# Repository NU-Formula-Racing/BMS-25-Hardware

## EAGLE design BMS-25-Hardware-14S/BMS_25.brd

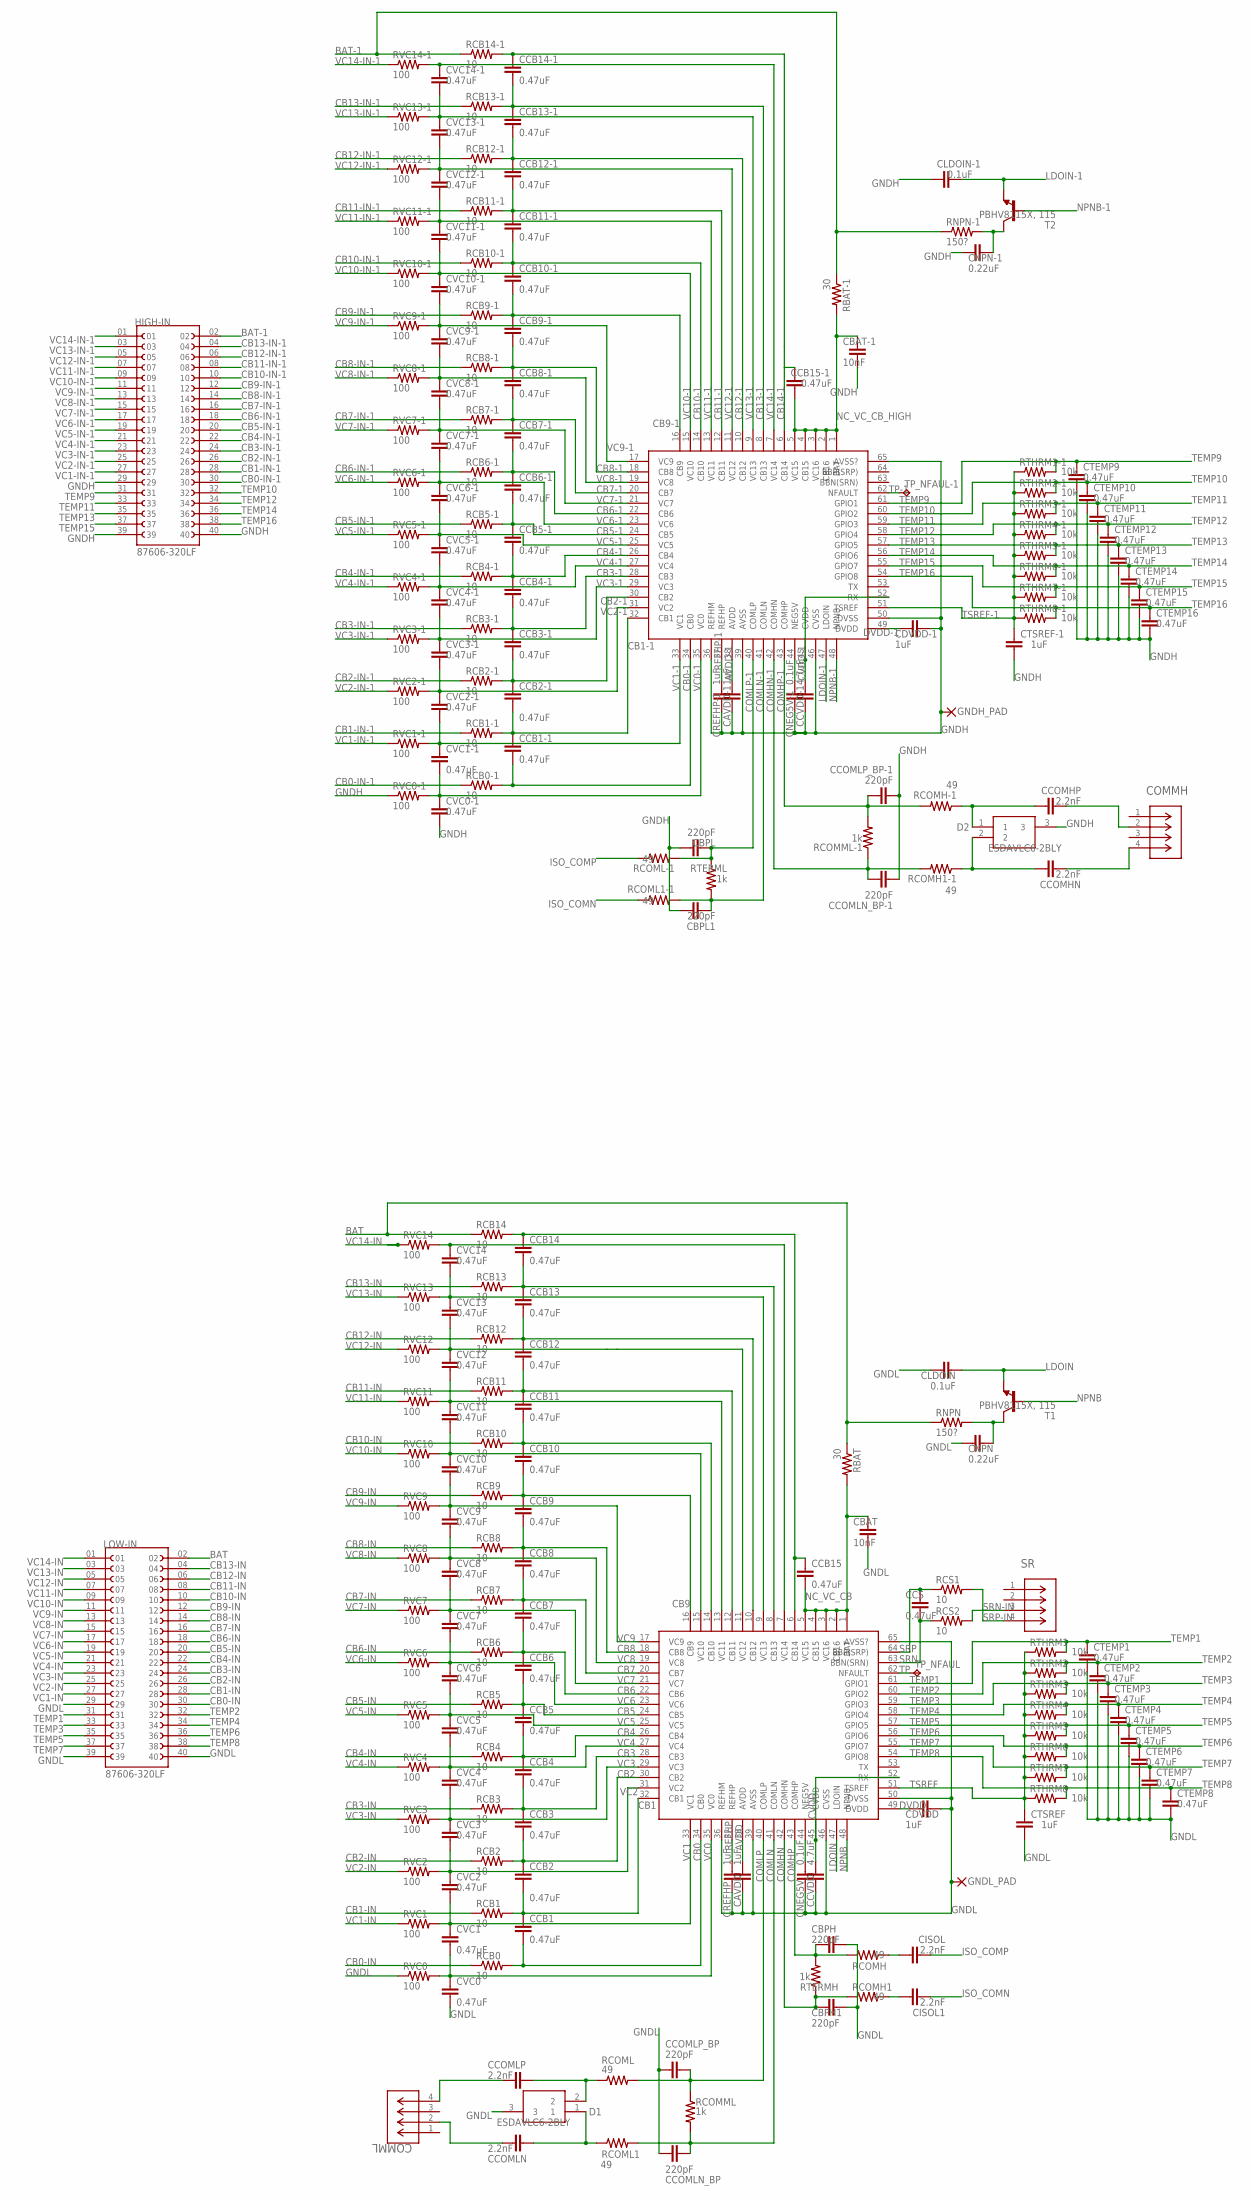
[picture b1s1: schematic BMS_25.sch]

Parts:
CAVDD: 1uF; C0603
CAVDD-1: 1uF; C0603
CBAT: 10nF; C0603
CBAT-1: 10nF; C0603
CBPH, CBPH1: 220pF; C0603
CBPL, CBPL1: 220pF; C0603
CCB1, CCB1-1, CCB2, CCB2-1, CCB3, CCB3-1, CCB4, CCB4-1, CCB5, CCB5-1, CCB6, CCB6-1, CCB7, CCB7-1, CCB8, CCB8-1, CCB9, CCB9-1, CCB10, CCB10-1, CCB11, CCB11-1, CCB12, CCB12-1, CCB13, CCB13-1, CCB14, CCB14-1, CCB15, CCB15-1: 0.47uF; C0603
CCOMHN: 2.2nF; C0603
CCOMHP: 2.2nF; C0603
CCOMLN: 2.2nF; C0603
CCOMLN_BP: 220pF; C0603
CCOMLN_BP-1: 220pF; C0603
CCOMLP: 2.2nF; C0603
CCOMLP_BP: 220pF; C0603
CCOMLP_BP-1: 220pF; C0603
CCS: 0.47uF; C0603
CCVDD: 4.7uF; C0603
CCVDD-1: 4.7uF; C0603
CDVDD: 1uF; C0603
CDVDD-1: 1uF; C0603
CISOL, CISOL1: 2.2nF; C0603
CLDOIN: 0.1uF; C0603
CLDOIN-1: 0.1uF; C0603
CNEG5V, CNEG5V-1: 0.1uF; C0603
CNPN: 0.22uF; C0603
CNPN-1: 0.22uF; C0603
COMMH: DF11-4DP-2DSA(24); CON4_2X2_UF_DF11_HIR
COMML: DF11-4DP-2DSA(24); CON4_2X2_UF_DF11_HIR
CREFHP: 1uF; C0603
CREFHP-1: 1uF; C0603
CTEMP1, CTEMP2, CTEMP3, CTEMP4, CTEMP5, CTEMP6, CTEMP7, CTEMP8, CTEMP9, CTEMP10, CTEMP11, CTEMP12, CTEMP13, CTEMP14, CTEMP15, CTEMP16: 0.47uF; C0603
CTSREF: 1uF; C0603
CTSREF-1: 1uF; C0603
CVC0, CVC0-1, CVC1, CVC1-1, CVC2, CVC2-1, CVC3, CVC3-1, CVC4, CVC4-1, CVC5, CVC5-1, CVC6, CVC6-1, CVC7, CVC7-1, CVC8, CVC8-1, CVC9, CVC9-1, CVC10, CVC10-1, CVC11, CVC11-1, CVC12, CVC12-1, CVC13, CVC13-1, CVC14, CVC14-1: 0.47uF; C0603
D1, D2: ESDAVLC6-2BLY; SOT95P255X150-3N
GNDH_PAD: SMD2; SMD1,27-2,54
GNDL_PAD: SMD2; SMD1,27-2,54
HIGH-IN: 87606-320LF; AMPHENOL_87606-320LF
IC1, IC2: PBQ79656PAPTQ1; QFP50P1200X1200X120-65N
LOW-IN: 87606-320LF; AMPHENOL_87606-320LF
RBAT: 30; R0603
RBAT-1: 30; R0603
RCB0, RCB0-1, RCB1, RCB1-1, RCB2, RCB2-1, RCB3, RCB3-1, RCB4, RCB4-1, RCB5, RCB5-1, RCB6, RCB6-1, RCB7, RCB7-1, RCB8, RCB8-1, RCB9, RCB9-1, RCB10, RCB10-1, RCB11, RCB11-1, RCB12, RCB12-1, RCB13, RCB13-1, RCB14, RCB14-1: 10; R2010
RCOMH, RCOMH1, RCOMH1-1: 49; R0603
RCOMH-1: 49; R0603
RCOML, RCOML1, RCOML1-1: 49; R0603
RCOML-1: 49; R0603
RCOMML: 1k; R0603
RCOMML-1: 1k; R0603
RCS1, RCS2: 10; R0603
RNPN: 150?; R2512W
RNPN-1: 150?; R2512W
RTERMH: 1k; R0603
RTERML: 1k; R0603
RTHRM1, RTHRM1-1, RTHRM2, RTHRM2-1, RTHRM3, RTHRM3-1, RTHRM4, RTHRM4-1, RTHRM5, RTHRM5-1, RTHRM6, RTHRM6-1, RTHRM7, RTHRM7-1, RTHRM8, RTHRM8-1: 10k; R0603
RVC0, RVC0-1, RVC1, RVC1-1, RVC2, RVC2-1, RVC3, RVC3-1, RVC4, RVC4-1, RVC5, RVC5-1, RVC6, RVC6-1, RVC7, RVC7-1, RVC8, RVC8-1, RVC9, RVC9-1, RVC10, RVC10-1, RVC11, RVC11-1, RVC12, RVC12-1, RVC13, RVC13-1, RVC14, RVC14-1: 100; R0603
SR: DF11-4DP-2DSA(24); CON4_2X2_UF_DF11_HIR
T1, T2: PBHV8115X, 115; SOT89-BCE
TP_NFAUL: TPB2,54; B2,54
TP_NFAUL-1: TPB2,54; B2,54

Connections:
AVDD: CAVDD.1, IC2.38 (AVDD)
AVDD-1: CAVDD-1.1, IC1.38 (AVDD)
BAT: LOW-IN.02, RBAT.1, RCB14.1, RNPN.1; also elsewhere on the board
BAT-1: HIGH-IN.02, RBAT-1.1, RCB14-1.1, RNPN-1.1; also elsewhere on the board
CB0: CCB1.2, IC2.34 (CB0), RCB0.2
CB0-1: CCB1-1.2, IC1.34 (CB0), RCB0-1.2
CB0-IN: LOW-IN.30, RCB0.1; also elsewhere on the board
CB0-IN-1: HIGH-IN.30, RCB0-1.1; also elsewhere on the board
CB1: CCB1.1, CCB2.2, IC2.32 (CB1), RCB1.2
CB1-1: CCB1-1.1, CCB2-1.2, IC1.32 (CB1), RCB1-1.2
CB1-IN: LOW-IN.28, RCB1.1; also elsewhere on the board
CB1-IN-1: HIGH-IN.28, RCB1-1.1; also elsewhere on the board
CB2: CCB2.1, CCB3.2, IC2.30 (CB2), RCB2.2
CB2-1: CCB2-1.1, CCB3-1.2, IC1.30 (CB2), RCB2-1.2
CB2-IN: LOW-IN.26, RCB2.1; also elsewhere on the board
CB2-IN-1: HIGH-IN.26, RCB2-1.1; also elsewhere on the board
CB3: CCB3.1, CCB4.2, IC2.28 (CB3), RCB3.2
CB3-1: CCB3-1.1, CCB4-1.2, IC1.28 (CB3), RCB3-1.2
CB3-IN: LOW-IN.24, RCB3.1; also elsewhere on the board
CB3-IN-1: HIGH-IN.24, RCB3-1.1; also elsewhere on the board
CB4: CCB4.1, CCB5.2, IC2.26 (CB4), RCB4.2
CB4-1: CCB4-1.1, CCB5-1.2, IC1.26 (CB4), RCB4-1.2
CB4-IN: LOW-IN.22, RCB4.1; also elsewhere on the board
CB4-IN-1: HIGH-IN.22, RCB4-1.1; also elsewhere on the board
CB5: CCB5.1, CCB6.2, IC2.24 (CB5), RCB5.2
CB5-1: CCB5-1.1, CCB6-1.2, IC1.24 (CB5), RCB5-1.2
CB5-IN: LOW-IN.20, RCB5.1; also elsewhere on the board
CB5-IN-1: HIGH-IN.20, RCB5-1.1; also elsewhere on the board
CB6: CCB6.1, CCB7.2, IC2.22 (CB6), RCB6.2
CB6-1: CCB6-1.1, CCB7-1.2, IC1.22 (CB6), RCB6-1.2
CB6-IN: LOW-IN.18, RCB6.1; also elsewhere on the board
CB6-IN-1: HIGH-IN.18, RCB6-1.1; also elsewhere on the board
CB7: CCB7.1, CCB8.2, IC2.20 (CB7), RCB7.2
CB7-1: CCB7-1.1, CCB8-1.2, IC1.20 (CB7), RCB7-1.2
CB7-IN: LOW-IN.16, RCB7.1; also elsewhere on the board
CB7-IN-1: HIGH-IN.16, RCB7-1.1; also elsewhere on the board
CB8: CCB8.1, CCB9.2, IC2.18 (CB8), RCB8.2
CB8-1: CCB8-1.1, CCB9-1.2, IC1.18 (CB8), RCB8-1.2
CB8-IN: LOW-IN.14, RCB8.1; also elsewhere on the board
CB8-IN-1: HIGH-IN.14, RCB8-1.1; also elsewhere on the board
CB9: CCB9.1, CCB10.2, IC2.16 (CB9), RCB9.2
CB9-1: CCB9-1.1, CCB10-1.2, IC1.16 (CB9), RCB9-1.2
CB9-IN: LOW-IN.12, RCB9.1; also elsewhere on the board
CB9-IN-1: HIGH-IN.12, RCB9-1.1; also elsewhere on the board
CB10: CCB10.1, CCB11.2, IC2.14 (CB10), RCB10.2
CB10-1: CCB10-1.1, CCB11-1.2, IC1.14 (CB10), RCB10-1.2
CB10-IN: LOW-IN.10, RCB10.1; also elsewhere on the board
CB10-IN-1: HIGH-IN.10, RCB10-1.1; also elsewhere on the board
CB11: CCB11.1, CCB12.2, IC2.12 (CB11), RCB11.2
CB11-1: CCB11-1.1, CCB12-1.2, IC1.12 (CB11), RCB11-1.2
CB11-IN: LOW-IN.08, RCB11.1; also elsewhere on the board
CB11-IN-1: HIGH-IN.08, RCB11-1.1; also elsewhere on the board
CB12: CCB12.1, CCB13.2, IC2.10 (CB12), RCB12.2
CB12-1: CCB12-1.1, CCB13-1.2, IC1.10 (CB12), RCB12-1.2
CB12-IN: LOW-IN.06, RCB12.1; also elsewhere on the board
CB12-IN-1: HIGH-IN.06, RCB12-1.1; also elsewhere on the board
CB13: CCB13.1, CCB14.2, IC2.8 (CB13), RCB13.2
CB13-1: CCB13-1.1, CCB14-1.2, IC1.8 (CB13), RCB13-1.2
CB13-IN: LOW-IN.04, RCB13.1; also elsewhere on the board
CB13-IN-1: HIGH-IN.04, RCB13-1.1; also elsewhere on the board
CB14: CCB14.1, CCB15.2, IC2.6 (CB14), RCB14.2
CB14-1: CCB14-1.1, CCB15-1.2, IC1.6 (CB14), RCB14-1.2
COMHN: CBPH1.1, IC2.42 (COMHN), RCOMH1.2, RTERMH.1
COMHN-1: CCOMLN_BP-1.1, IC1.42 (COMHN), RCOMH1-1.2, RCOMML-1.1
COMHP: CBPH.1, IC2.43 (COMHP), RCOMH.2, RTERMH.2
COMHP-1: CCOMLP_BP-1.1, IC1.43 (COMHP), RCOMH-1.2, RCOMML-1.2
COMLN: CCOMLN_BP.1, IC2.41 (COMLN), RCOML1.2, RCOMML.2
COMLN-1: CBPL1.1, IC1.41 (COMLN), RCOML1-1.2, RTERML.2
COMLP: CCOMLP_BP.1, IC2.40 (COMLP), RCOML.2, RCOMML.1
COMLP-1: CBPL.1, IC1.40 (COMLP), RCOML-1.2, RTERML.1
CVDD: CCVDD.1, IC2.45 (CVDD), IC2.52 (RX)
CVDD-1: CCVDD-1.1, IC1.45 (CVDD), IC1.52 (RX)
DVDD: CDVDD.1, IC2.49 (DVDD)
DVDD-1: CDVDD-1.1, IC1.49 (DVDD)
ISO_COMN: CISOL1.1, RCOML1-1.1; also elsewhere on the board
ISO_COMP: CISOL.1, RCOML-1.1; also elsewhere on the board
LDOIN: CLDOIN.1, IC2.47 (LDOIN), T1.E
LDOIN-1: CLDOIN-1.1, IC1.47 (LDOIN), T2.E
unnamed 79: CNPN.2, RNPN.2, T1.C; also elsewhere on the board
unnamed: CNEG5V.1, IC2.44 (NEG5V)
unnamed 81: CISOL.2, RCOMH.1; also elsewhere on the board
unnamed 82: CISOL1.2, RCOMH1.1; also elsewhere on the board
unnamed 83: CCOMLN.2, D1.1, RCOML1.1; also elsewhere on the board
unnamed 84: CCOMLP.2, D1.2, RCOML.1; also elsewhere on the board
unnamed: CNEG5V-1.1, IC1.44 (NEG5V)
unnamed 86: CNPN-1.2, RNPN-1.2, T2.C; also elsewhere on the board
unnamed 87: CCOMHP.2, D2.1, RCOMH-1.1; also elsewhere on the board
unnamed 88: CCOMHN.2, D2.2, RCOMH1-1.1; also elsewhere on the board
unnamed 89: CCOMHP.1, COMMH.2; also elsewhere on the board
unnamed 90: CCOMHN.1, COMMH.4; also elsewhere on the board
unnamed 91: CCOMLN.1, COMML.2; also elsewhere on the board
unnamed 92: CCOMLP.1, COMML.4; also elsewhere on the board
NC_VC_CB: CBAT.2, CCB15.1, IC2.1 (BAT), IC2.2 (CB16), IC2.3 (VC16), IC2.4 (CB15), IC2.5 (VC15), RBAT.2
NC_VC_CB_HIGH: CBAT-1.2, CCB15-1.1, IC1.1 (BAT), IC1.2 (CB16), IC1.3 (VC16), IC1.4 (CB15), IC1.5 (VC15), RBAT-1.2
NPNB: IC2.48 (NPNB), T1.B
NPNB-1: IC1.48 (NPNB), T2.B
REFHP: CREFHP.1, IC2.37 (REFHP)
REFHP-1: CREFHP-1.1, IC1.37 (REFHP)
SRN: CCS.1, IC2.63 (BBN(SRN)), RCS2.1
SRN-IN: RCS2.2, SR.3
SRP: CCS.2, IC2.64 (BBP(SRP)), RCS1.1
SRP-IN: RCS1.2, SR.4
TEMP1: CTEMP1.1, IC2.61 (GPIO1), LOW-IN.31, RTHRM1.2; also elsewhere on the board
TEMP2: CTEMP2.1, IC2.60 (GPIO2), LOW-IN.32, RTHRM2.2; also elsewhere on the board
TEMP3: CTEMP3.1, IC2.59 (GPIO3), LOW-IN.33, RTHRM3.2; also elsewhere on the board
TEMP4: CTEMP4.1, IC2.58 (GPIO4), LOW-IN.34, RTHRM4.2; also elsewhere on the board
TEMP5: CTEMP5.1, IC2.57 (GPIO5), LOW-IN.35, RTHRM5.2; also elsewhere on the board
TEMP6: CTEMP6.1, IC2.56 (GPIO6), LOW-IN.36, RTHRM6.2; also elsewhere on the board
TEMP7: CTEMP7.1, IC2.55 (GPIO7), LOW-IN.37, RTHRM7.2; also elsewhere on the board
TEMP8: CTEMP8.1, IC2.54 (GPIO8), LOW-IN.38, RTHRM8.2; also elsewhere on the board
TEMP9: CTEMP9.1, HIGH-IN.31, IC1.61 (GPIO1), RTHRM1-1.2; also elsewhere on the board
TEMP10: CTEMP10.1, HIGH-IN.32, IC1.60 (GPIO2), RTHRM2-1.2; also elsewhere on the board
TEMP11: CTEMP11.1, HIGH-IN.33, IC1.59 (GPIO3), RTHRM3-1.2; also elsewhere on the board
TEMP12: CTEMP12.1, HIGH-IN.34, IC1.58 (GPIO4), RTHRM4-1.2; also elsewhere on the board
TEMP13: CTEMP13.1, HIGH-IN.35, IC1.57 (GPIO5), RTHRM5-1.2; also elsewhere on the board
TEMP14: CTEMP14.1, HIGH-IN.36, IC1.56 (GPIO6), RTHRM6-1.2; also elsewhere on the board
TEMP15: CTEMP15.1, HIGH-IN.37, IC1.55 (GPIO7), RTHRM7-1.2; also elsewhere on the board
TEMP16: CTEMP16.1, HIGH-IN.38, IC1.54 (GPIO8), RTHRM8-1.2; also elsewhere on the board
TP: IC2.62 (NFAULT), TP_NFAUL.TP; also elsewhere on the board
TP-1: IC1.62 (NFAULT), TP_NFAUL-1.TP; also elsewhere on the board
TSREF: CTSREF.1, IC2.51 (TSREF), RTHRM1.1, RTHRM2.1, RTHRM3.1, RTHRM4.1, RTHRM5.1, RTHRM6.1, RTHRM7.1, RTHRM8.1
TSREF-1: CTSREF-1.1, IC1.51 (TSREF), RTHRM1-1.1, RTHRM2-1.1, RTHRM3-1.1, RTHRM4-1.1, RTHRM5-1.1, RTHRM6-1.1, RTHRM7-1.1, RTHRM8-1.1
VC0: CVC0.1, CVC1.2, IC2.35 (VC0), RVC0.2
VC0-1: CVC0-1.1, CVC1-1.2, IC1.35 (VC0), RVC0-1.2
VC1: CVC1.1, CVC2.2, IC2.33 (VC1), RVC1.2
VC1-1: CVC1-1.1, CVC2-1.2, IC1.33 (VC1), RVC1-1.2
VC1-IN: LOW-IN.27, RVC1.1; also elsewhere on the board
VC1-IN-1: HIGH-IN.27, RVC1-1.1; also elsewhere on the board
VC2: CVC2.1, CVC3.2, IC2.31 (VC2), RVC2.2
VC2-1: CVC2-1.1, CVC3-1.2, IC1.31 (VC2), RVC2-1.2
VC2-IN: LOW-IN.25, RVC2.1; also elsewhere on the board
VC2-IN-1: HIGH-IN.25, RVC2-1.1; also elsewhere on the board
VC3: CVC3.1, CVC4.2, IC2.29 (VC3), RVC3.2
VC3-1: CVC3-1.1, CVC4-1.2, IC1.29 (VC3), RVC3-1.2
VC3-IN: LOW-IN.23, RVC3.1; also elsewhere on the board
VC3-IN-1: HIGH-IN.23, RVC3-1.1; also elsewhere on the board
VC4: CVC4.1, CVC5.2, IC2.27 (VC4), RVC4.2
VC4-1: CVC4-1.1, CVC5-1.2, IC1.27 (VC4), RVC4-1.2
VC4-IN: LOW-IN.21, RVC4.1; also elsewhere on the board
VC4-IN-1: HIGH-IN.21, RVC4-1.1; also elsewhere on the board
VC5: CVC5.1, CVC6.2, IC2.25 (VC5), RVC5.2
VC5-1: CVC5-1.1, CVC6-1.2, IC1.25 (VC5), RVC5-1.2
VC5-IN: LOW-IN.19, RVC5.1; also elsewhere on the board
VC5-IN-1: HIGH-IN.19, RVC5-1.1; also elsewhere on the board
VC6: CVC6.1, CVC7.2, IC2.23 (VC6), RVC6.2
VC6-1: CVC6-1.1, CVC7-1.2, IC1.23 (VC6), RVC6-1.2
VC6-IN: LOW-IN.17, RVC6.1; also elsewhere on the board
VC6-IN-1: HIGH-IN.17, RVC6-1.1; also elsewhere on the board
VC7: CVC7.1, CVC8.2, IC2.21 (VC7), RVC7.2
VC7-1: CVC7-1.1, CVC8-1.2, IC1.21 (VC7), RVC7-1.2
VC7-IN: LOW-IN.15, RVC7.1; also elsewhere on the board
VC7-IN-1: HIGH-IN.15, RVC7-1.1; also elsewhere on the board
VC8: CVC8.1, CVC9.2, IC2.19 (VC8), RVC8.2
VC8-1: CVC8-1.1, CVC9-1.2, IC1.19 (VC8), RVC8-1.2
VC8-IN: LOW-IN.13, RVC8.1; also elsewhere on the board
VC8-IN-1: HIGH-IN.13, RVC8-1.1; also elsewhere on the board
VC9: CVC9.1, CVC10.2, IC2.17 (VC9), RVC9.2
VC9-1: CVC9-1.1, CVC10-1.2, IC1.17 (VC9), RVC9-1.2
VC9-IN: LOW-IN.11, RVC9.1; also elsewhere on the board
VC9-IN-1: HIGH-IN.11, RVC9-1.1; also elsewhere on the board
VC10: CVC10.1, CVC11.2, IC2.15 (VC10), RVC10.2
VC10-1: CVC10-1.1, CVC11-1.2, IC1.15 (VC10), RVC10-1.2
VC10-IN: LOW-IN.09, RVC10.1; also elsewhere on the board
VC10-IN-1: HIGH-IN.09, RVC10-1.1; also elsewhere on the board
VC11: CVC11.1, CVC12.2, IC2.13 (VC11), RVC11.2
VC11-1: CVC11-1.1, CVC12-1.2, IC1.13 (VC11), RVC11-1.2
VC11-IN: LOW-IN.07, RVC11.1; also elsewhere on the board
VC11-IN-1: HIGH-IN.07, RVC11-1.1; also elsewhere on the board
VC12: CVC12.1, CVC13.2, IC2.11 (VC12), RVC12.2
VC12-1: CVC12-1.1, CVC13-1.2, IC1.11 (VC12), RVC12-1.2
VC12-IN: LOW-IN.05, RVC12.1; also elsewhere on the board
VC12-IN-1: HIGH-IN.05, RVC12-1.1; also elsewhere on the board
VC13: CVC13.1, CVC14.2, IC2.9 (VC13), RVC13.2
VC13-1: CVC13-1.1, CVC14-1.2, IC1.9 (VC13), RVC13-1.2
VC13-IN: LOW-IN.03, RVC13.1; also elsewhere on the board
VC13-IN-1: HIGH-IN.03, RVC13-1.1; also elsewhere on the board
VC14: CVC14.1, IC2.7 (VC14), RVC14.2
VC14-1: CVC14-1.1, IC1.7 (VC14), RVC14-1.2
VC14-IN: LOW-IN.01, RVC14.1; also elsewhere on the board
VC14-IN-1: HIGH-IN.01, RVC14-1.1; also elsewhere on the board

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
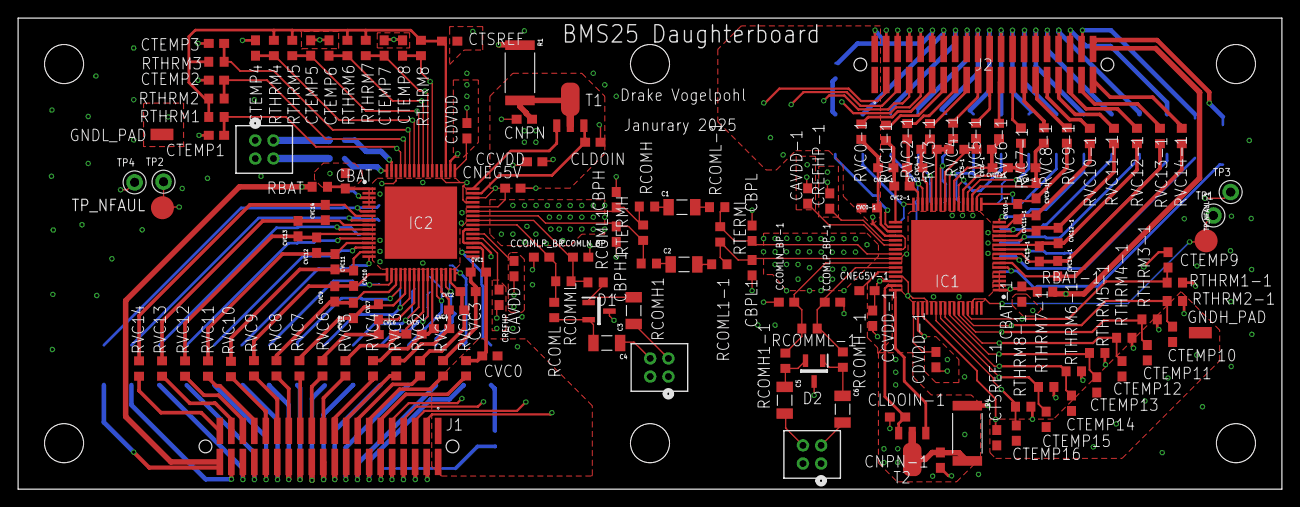
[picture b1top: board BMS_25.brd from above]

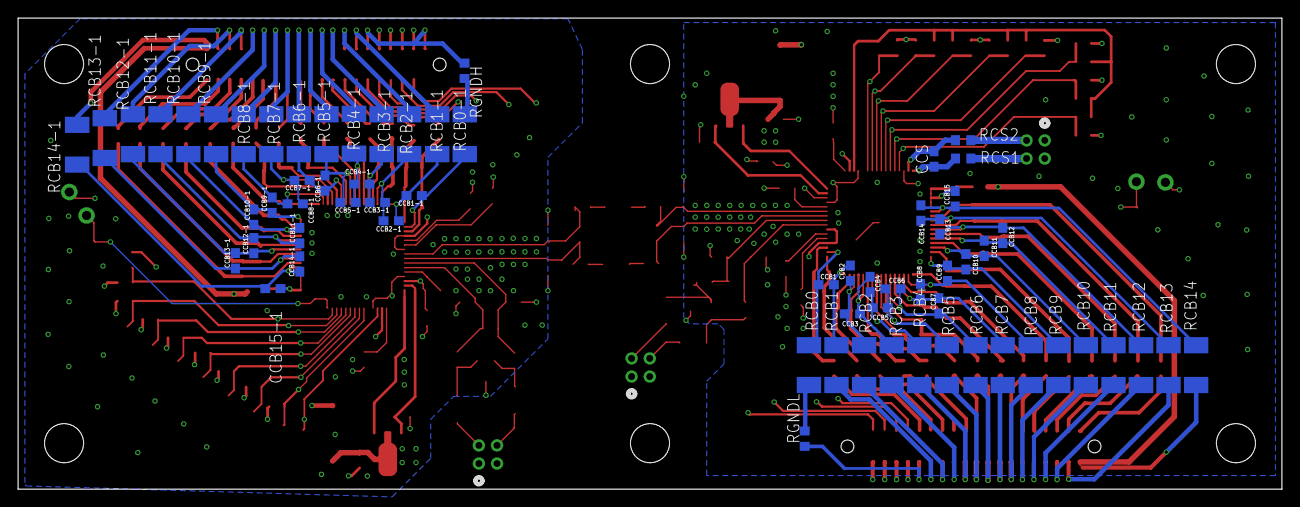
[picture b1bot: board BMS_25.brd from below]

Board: 4 copper layers, 139.7 x 52.1 mm, 224 parts (65 on the bottom side), 184 nets.

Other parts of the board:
C1, C2, C3, C4, C5, C6: C1206C105K5RACTU; CAPC3216X120N
J1, J2: TFM-120-02-L-D-A; TFM-120-ZZ-XXX-D-A
R1, R4: RC2512JK-07560RL; RESC6331X65N
RGNDH: 0; R0603
RGNDL: 0; R0603
TP1, TP2, TP3, TP4: 5002; KEYSTONE_5002

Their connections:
BAT: J1.40, R1.1; also elsewhere on the board
BAT-1: J2.40, R4.1; also elsewhere on the board
CB0-IN: RGNDL.2; also elsewhere on the board
CB0-IN-1: RGNDH.2; also elsewhere on the board
CB1-IN: J1.14; also elsewhere on the board
CB1-IN-1: J2.14; also elsewhere on the board
CB2-IN: J1.16; also elsewhere on the board
CB2-IN-1: J2.16; also elsewhere on the board
CB3-IN: J1.18; also elsewhere on the board
CB3-IN-1: J2.18; also elsewhere on the board
CB4-IN: J1.20; also elsewhere on the board
CB4-IN-1: J2.20; also elsewhere on the board
CB5-IN: J1.22; also elsewhere on the board
CB5-IN-1: J2.22; also elsewhere on the board
CB6-IN: J1.24; also elsewhere on the board
CB6-IN-1: J2.24; also elsewhere on the board
CB7-IN: J1.26; also elsewhere on the board
CB7-IN-1: J2.26; also elsewhere on the board
CB8-IN: J1.28; also elsewhere on the board
CB8-IN-1: J2.28; also elsewhere on the board
CB9-IN: J1.30; also elsewhere on the board
CB9-IN-1: J2.30; also elsewhere on the board
CB10-IN: J1.32; also elsewhere on the board
CB10-IN-1: J2.32; also elsewhere on the board
CB11-IN: J1.34; also elsewhere on the board
CB11-IN-1: J2.34; also elsewhere on the board
CB12-IN: J1.36; also elsewhere on the board
CB12-IN-1: J2.36; also elsewhere on the board
CB13-IN: J1.38; also elsewhere on the board
CB13-IN-1: J2.38; also elsewhere on the board
ISO_COMN: C2.2; also elsewhere on the board
ISO_COMP: C1.2; also elsewhere on the board
unnamed 79: R1.2; also elsewhere on the board
unnamed 81: C1.1; also elsewhere on the board
unnamed 82: C2.1; also elsewhere on the board
unnamed 83: C3.2; also elsewhere on the board
unnamed 84: C4.2; also elsewhere on the board
unnamed 86: R4.2; also elsewhere on the board
unnamed 87: C6.1; also elsewhere on the board
unnamed 88: C5.1; also elsewhere on the board
unnamed 89: C6.2; also elsewhere on the board
unnamed 90: C5.2; also elsewhere on the board
unnamed 91: C3.1; also elsewhere on the board
unnamed 92: C4.1; also elsewhere on the board
TEMP1: J1.9; also elsewhere on the board
TEMP2: J1.10; also elsewhere on the board
TEMP3: J1.7; also elsewhere on the board
TEMP4: J1.8; also elsewhere on the board
TEMP5: J1.5; also elsewhere on the board
TEMP6: J1.6; also elsewhere on the board
TEMP7: J1.3; also elsewhere on the board
TEMP8: J1.4; also elsewhere on the board
TEMP9: J2.9; also elsewhere on the board
TEMP10: J2.10; also elsewhere on the board
TEMP11: J2.7; also elsewhere on the board
TEMP12: J2.8; also elsewhere on the board
TEMP13: J2.5; also elsewhere on the board
TEMP14: J2.6; also elsewhere on the board
TEMP15: J2.3; also elsewhere on the board
TEMP16: J2.4; also elsewhere on the board
TP: TP2.TP; also elsewhere on the board
TP-1: TP1.TP; also elsewhere on the board
VC1-IN: J1.13; also elsewhere on the board
VC1-IN-1: J2.13; also elsewhere on the board
VC2-IN: J1.15; also elsewhere on the board
VC2-IN-1: J2.15; also elsewhere on the board
VC3-IN: J1.17; also elsewhere on the board
VC3-IN-1: J2.17; also elsewhere on the board
VC4-IN: J1.19; also elsewhere on the board
VC4-IN-1: J2.19; also elsewhere on the board
VC5-IN: J1.21; also elsewhere on the board
VC5-IN-1: J2.21; also elsewhere on the board
VC6-IN: J1.23; also elsewhere on the board
VC6-IN-1: J2.23; also elsewhere on the board
VC7-IN: J1.25; also elsewhere on the board
VC7-IN-1: J2.25; also elsewhere on the board
VC8-IN: J1.27; also elsewhere on the board
VC8-IN-1: J2.27; also elsewhere on the board
VC9-IN: J1.29; also elsewhere on the board
VC9-IN-1: J2.29; also elsewhere on the board
VC10-IN: J1.31; also elsewhere on the board
VC10-IN-1: J2.31; also elsewhere on the board
VC11-IN: J1.33; also elsewhere on the board
VC11-IN-1: J2.33; also elsewhere on the board
VC12-IN: J1.35; also elsewhere on the board
VC12-IN-1: J2.35; also elsewhere on the board
VC13-IN: J1.37; also elsewhere on the board
VC13-IN-1: J2.37; also elsewhere on the board
VC14-IN: J1.39; also elsewhere on the board
VC14-IN-1: J2.39; also elsewhere on the board

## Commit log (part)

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2024-07-23 Added WIP of BMS25 Daughterboard
    Still need to fix DRC errors (ie passive keepout regions (or delete them lol)). Would also like a second set of eyes before being sent out.
2024-07-23 Added WIP STEP file
2024-08-05 Passed DRC
2024-08-05 Added CAD files with header in Assembly
2025-01-10 Added 14S design
2025-01-10 14S Design
2025-01-11 Switched BAT to CB instead of VC line
2025-01-11 Fixed Ground wiring
2025-01-14 Changed Connectors, pass DRC
2025-02-14 Updated Change to daughteboard 14s for final manufacturing
2025-02-15 Daughterboard Updated

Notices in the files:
parts and their libraries:
COPYRIGHT: Copyright (C) 2023 Ultra Librarian. All rights reserved.
BMS24: COPYRIGHT: Copyright (C) 2024 Ultra Librarian. All rights reserved.
